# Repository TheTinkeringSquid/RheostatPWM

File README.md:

# Dodge B2500 Instrument Cluster LED PWM Dimmer

Small RP2040-based PWM dimmer board for a 1996 Dodge B2500 instrument cluster
LED conversion. It reads the factory headlight rheostat as an analog input and
drives the cluster illumination feed with a protected high-side 12 V PWM output.

> **Cluster illumination only.** This board is not for exterior lighting, brake
> lights, turn signals, airbags, engine controls, or any safety-critical
> circuit.

---

## How it works

```
factory full 12 V illumination/headlamp-switched feed  -> J1 VIN_RAW
factory dimmer/rheostat analog output                  -> J1 DIM_IN  (sense only)
board high-side 12 V PWM output                        -> J1 PWM_OUT -> cluster LED +
cluster/chassis ground                                 -> J1 GND
```

The factory rheostat no longer powers the cluster lamps. It is read as a
low-current analog control signal through a high-impedance divider into the
XIAO RP2040 ADC. Firmware maps that voltage through a gamma curve to a high-side
PWM output (P-channel MOSFET Q1 driven by N-MOSFET Q2), so the lamp grounds stay
factory.

### Connector (J1)

| Pin | Net        | Description                                            |
|----:|------------|--------------------------------------------------------|
| 1   | `VIN_RAW`  | Fused full 12 V illumination/headlight-switched feed   |
| 2   | `GND`      | Chassis/cluster ground                                 |
| 3   | `DIM_IN`   | Factory rheostat output, sense only                    |
| 4   | `PWM_OUT`  | PWM +12 V output to cluster LED illumination feed      |
| 5   | `IGN_SENSE`| Optional lights-on signal (future firmware; DNP parts) |

### Install concept

1. Identify the factory cluster illumination/dimmer feed with a multimeter and
   wiring diagram.
2. Cut or depin the cluster illumination feed so the rheostat no longer powers
   the LED bulbs directly.
3. Connect the **vehicle/rheostat side** of that wire to `DIM_IN`.
4. Connect the **cluster/lamp side** of that wire to `PWM_OUT`.
5. Power the board from a fused full-bright illumination feed that is hot when
   park/headlights are on — **not** from the dimmed rheostat output.
6. Ground the board to the cluster/chassis ground.

> Do **not** power the microcontroller from `DIM_IN`; it may brown out when the
> rheostat is turned down.
>
> If the factory dimmer turns out to be low-side, already-PWM, or multiplexed
> rather than a simple variable positive voltage, **stop** and revise the input
> circuit instead of forcing this design.

---

## Repository layout

```
.
├── README.md
├── firmware/                     PlatformIO project (Seeed XIAO RP2040)
│   ├── platformio.ini
│   └── src/main.cpp
└── hardware/
    ├── kicad/
    │   ├── b2500_cluster_pwm_dimmer.kicad_pro / .kicad_sch / .kicad_pcb
    │   ├── b2500_cluster_pwm_dimmer_schematic.pdf
    │   ├── pcb_top.png
    │   └── symbols_and_footprints/b2500.pretty/   (XIAO + Pololu module footprints)
    ├── scripts/                  generators (re-create the design deterministically)
    │   ├── netlist.py            single source of truth for the netlist
    │   ├── gen_sch.py            -> kicad_sch
    │   ├── gen_pcb.py            -> kicad_pcb
    │   ├── gen_bom.py            -> BOM CSV
    │   └── export_fab.py         -> gerbers + drill + BOM (run after routing)
    ├── gerbers/                  fabrication output (generated after routing)
    ├── fabrication_notes.md
    └── b2500_cluster_pwm_dimmer_bom.csv
```

The KiCad schematic, board, and BOM are generated by the scripts in
`hardware/scripts/`. They share `netlist.py` so the schematic and board can
never drift apart. Regenerate with:

```powershell
python hardware/scripts/gen_sch.py                       # schematic
& "C:/Program Files/KiCad/10.0/bin/python.exe" hardware/scripts/gen_pcb.py   # board (needs KiCad's Python)
python hardware/scripts/gen_bom.py                       # BOM CSV
```

---

## Firmware

Built with PlatformIO for the Seeed Studio XIAO RP2040 (Arduino / Earle
Philhower RP2040 core).

```bash
cd firmware
pio run            # build
pio run -t upload  # flash (board in UF2 bootloader, or via USB)
pio device monitor # 115200 baud serial debug
```

Key calibration constants live at the top of `firmware/src/main.cpp`
(`ADC_OFF_THRESHOLD`, `ADC_MIN_INPUT`, `ADC_MAX_INPUT`, `DUTY_MIN`, `GAMMA`,
`PWM_FREQ_HZ`, plus `REVERSE_DIMMER_DIRECTION`). Tune them on the bench against
the real dimmer using the serial output. PWM defaults to 976 Hz (in the
500 Hz–2 kHz target band).

---

## PCB

The board is **fully routed and DRC-clean** (0 violations, 0 unconnected) —
2 layers, 94 × 62 mm, ground pour on both. `hardware/scripts/gen_pcb.py`
places every part, pours ground, and routes all nets with a built-in
collision-aware router (Manhattan + maze fallback): high-current nets
(`VIN_RAW`, `PWM_OUT`, `VIN_PROT`) at 1.5 mm, signals at 0.4 mm. The gerbers and
drill files in `hardware/gerbers/` are ready to send to a fabricator.

You don't need to touch KiCad to get the board made. If you *want* to inspect or
tweak it:

1. Open `hardware/kicad/b2500_cluster_pwm_dimmer.kicad_pro` in KiCad 10.
2. Make changes, run DRC, then regenerate fabrication output:

   ```powershell
   python hardware/scripts/export_fab.py
   ```

   This runs DRC, writes gerbers + Excellon drill to `hardware/gerbers/`, and
   regenerates the BOM. (Re-running `gen_pcb.py` regenerates the whole board
   from scratch and will discard manual KiCad edits.)

### Ordering the board

Zip the contents of `hardware/gerbers/` and upload to any PCB fab (JLCPCB,
PCBWay, OSH Park, Aisler, etc.): 2-layer, 1.6 mm, 1 oz copper (2 oz is a nice
upgrade for the power path), HASL or ENIG. See
[hardware/fabrication_notes.md](hardware/fabrication_notes.md) for the full
spec, assembly notes, and the bench/in-vehicle test procedures.

---

## Deviations from the original brief

- **Board size** is ~94 × 62 mm, not the 50 × 35 mm target. The through-hole
  part set (5-pos 5.08 mm terminal block, TO-220, two modules, radial cap, seven
  test points, button) does not fit smaller while staying hand-solderable. A
  compact SMD-MOSFET / smaller-connector variant is a sensible future revision.
- **Q1 gate pull-up R6 is 10 k (brief said 47 k)** and a **DNP R10/C5 RC snubber
  footprint** sits across `PWM_OUT` — both for a cleaner, better-defined
  high-side switching edge with less ringing/EMI. Fit the snubber only if the
  bench scope shows ringing.
- **The buck regulator (U2) mounts off-board**, wired to a labeled 3-pin
  header (`VIN`/`GND`/`VOUT`). A footprint audit against the Pololu module
  showed its on-board land is easy to get wrong (6 pins incl. an offset PG, two
  GNDs); a wired connection is order-proof and far safer to assemble by hand.
- **Two M3 mounting holes** (per the BOM, M1–M2), placed diagonally — the
  terminal block fills the left edge, so a top-left hole was not possible.
- The board is routed by a **purpose-built script router**, not by hand in
  KiCad. It is DRC-clean and electrically complete, but the trace paths are
  Manhattan/maze-style rather than artistically dressed; feel free to prettify
  in the GUI if you re-spin.
- The XIAO USB-C port is not on a board edge; for in-place reflashing, prefer
  the UF2 bootloader or relocate U1 to an edge in a future revision.

## Safety

- Always fuse `VIN_RAW` (inline blade fuse in the harness — F1 is not on the
  board). Size it to the measured LED cluster current.
- Do not route the cluster output back through the factory rheostat.
- Do not connect USB while the board is vehicle-powered unless JP1 is open / the
  D3 isolation diode is fitted, to avoid 5 V backfeed.
- This is not OEM-grade load-dump protection. The TVS + wide-input regulator
  reduce risk but do not eliminate it.
- Carry a bypass jumper during early testing so the cluster lamps can be
  restored if the board fails.

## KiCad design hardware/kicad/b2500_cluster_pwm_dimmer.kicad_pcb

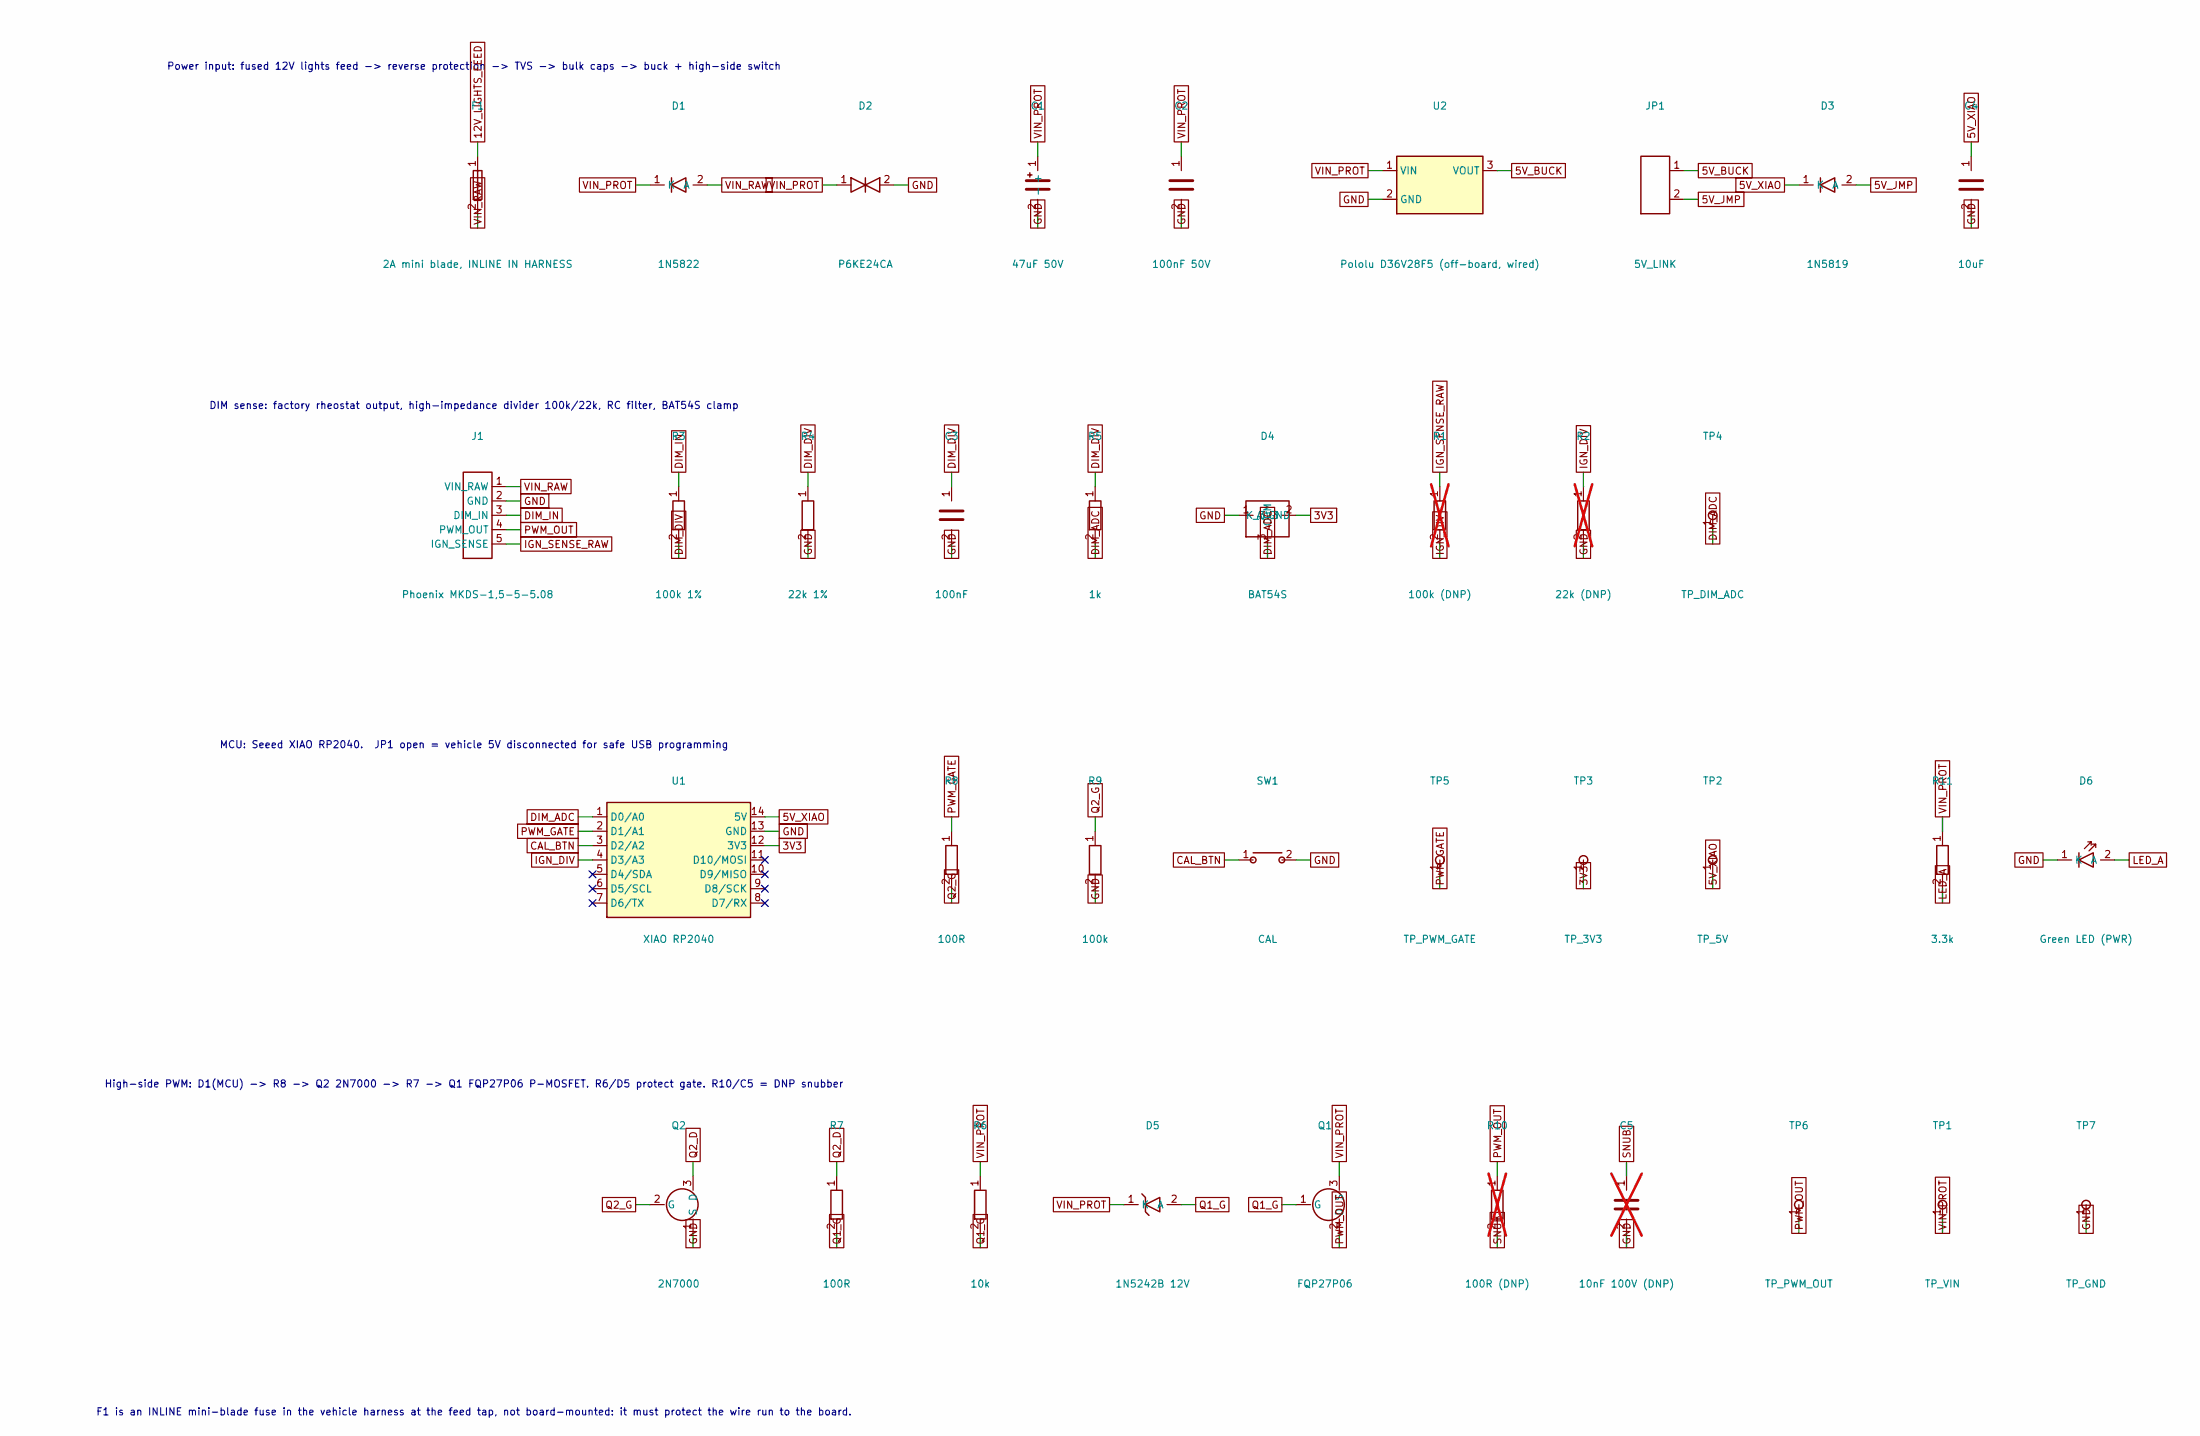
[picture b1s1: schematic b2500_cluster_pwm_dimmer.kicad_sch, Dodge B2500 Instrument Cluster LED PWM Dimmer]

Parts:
C1: 47uF 50V; CP_Radial_D6.3mm_P2.50mm
C2: 100nF 50V; C_0805_2012Metric_Pad1.18x1.45mm_HandSolder
C3: 100nF; C_0805_2012Metric_Pad1.18x1.45mm_HandSolder
C4: 10uF; C_0805_2012Metric_Pad1.18x1.45mm_HandSolder
C5: 10nF 100V (DNP); C_0805_2012Metric_Pad1.18x1.45mm_HandSolder; not fitted
D1: 1N5822; D_DO-201AD_P15.24mm_Horizontal
D2: P6KE24CA; D_DO-15_P10.16mm_Horizontal
D3: 1N5819; D_DO-41_SOD81_P10.16mm_Horizontal
D4: BAT54S; SOT-23
D5: 1N5242B 12V; D_DO-35_SOD27_P7.62mm_Horizontal
D6: Green LED (PWR); LED_D3.0mm
F1: 2A mini blade, INLINE IN HARNESS
J1: Phoenix MKDS-1,5-5-5.08; TerminalBlock_Phoenix_MKDS-1,5-5-5.08_1x05_P5.08mm_Horizont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
JP1: 5V_LINK; PinHeader_1x02_P2.54mm_Vertical
Q1: FQP27P06; TO-220-3_Vertical
Q2: 2N7000; TO-92_Inline_Wide
R1: 100k (DNP); R_0805_2012Metric_Pad1.20x1.40mm_HandSolder; not fitted
R2: 22k (DNP); R_0805_2012Metric_Pad1.20x1.40mm_HandSolder; not fitted
R3: 100k 1%; R_0805_2012Metric_Pad1.20x1.40mm_HandSolder
R4: 22k 1%; R_0805_2012Metric_Pad1.20x1.40mm_HandSolder
R5: 1k; R_0805_2012Metric_Pad1.20x1.40mm_HandSolder
R6: 10k; R_0805_2012Metric_Pad1.20x1.40mm_HandSolder
R7, R8: 100R; R_0805_2012Metric_Pad1.20x1.40mm_HandSolder
R9: 100k; R_0805_2012Metric_Pad1.20x1.40mm_HandSolder
R10: 100R (DNP); R_0805_2012Metric_Pad1.20x1.40mm_HandSolder; not fitted
R11: 3.3k; R_0805_2012Metric_Pad1.20x1.40mm_HandSolder
SW1: CAL; SW_PUSH_6mm
TP1: TP_VIN; TestPoint_THTPad_D1.5mm_Drill0.7mm
TP2: TP_5V; TestPoint_THTPad_D1.5mm_Drill0.7mm
TP3: TP_3V3; TestPoint_THTPad_D1.5mm_Drill0.7mm
TP4: TP_DIM_ADC; TestPoint_THTPad_D1.5mm_Drill0.7mm
TP5: TP_PWM_GATE; TestPoint_THTPad_D1.5mm_Drill0.7mm
TP6: TP_PWM_OUT; TestPoint_THTPad_D1.5mm_Drill0.7mm
TP7: TP_GND; TestPoint_THTPad_D1.5mm_Drill0.7mm
U1: XIAO RP2040; XIAO_RP2040_THT
U2: Pololu D36V28F5 (off-board, wired); PinHeader_1x03_P2.54mm_Vertical

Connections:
3V3: D4.2 (K_3V3), TP3.1, U1.12 (3V3)
5V_BUCK: JP1.1, U2.3 (VOUT)
5V_JMP: D3.2 (A), JP1.2
5V_XIAO: C4.1, D3.1 (K), TP2.1, U1.14 (5V)
CAL_BTN: SW1.1, U1.3 (D2/A2)
DIM_ADC: D4.3 (COM), R5.2, TP4.1, U1.1 (D0/A0)
DIM_DIV: C3.1, R3.2, R4.1, R5.1
DIM_IN: J1.3 (DIM_IN), R3.1
GND: C1.2 (-), C2.2, C3.2, C4.2, C5.2, D2.2, D4.1 (A_GND), D6.1 (K), J1.2 (GND), Q2.1 (S), R2.2, R4.2, R9.2, SW1.2, TP7.1, U1.13 (GND), U2.2 (GND)
IGN_DIV: R1.2, R2.1, U1.4 (D3/A3)
IGN_SENSE_RAW: J1.5 (IGN_SENSE), R1.1
LED_A: D6.2 (A), R11.2
PWM_GATE: R8.1, TP5.1, U1.2 (D1/A1)
PWM_OUT: J1.4 (PWM_OUT), Q1.2 (D), R10.1, TP6.1
Q1_G: D5.2 (A), Q1.1 (G), R6.2, R7.2
Q2_D: Q2.3 (D), R7.1
Q2_G: Q2.2 (G), R8.2, R9.1
SNUB: C5.1, R10.2
VIN_PROT: C1.1 (+), C2.1, D1.1 (K), D2.1, D5.1 (K), Q1.3 (S), R6.1, R11.1, TP1.1, U2.1 (VIN)
VIN_RAW: D1.2 (A), F1.2, J1.1 (VIN_RAW)

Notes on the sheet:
Power input: fused 12V lights feed -> reverse protection -> TVS -> bulk caps -> buck + high-side switch
DIM sense: factory rheostat output, high-impedance divider 100k/22k, RC filter, BAT54S clamp
MCU: Seeed XIAO RP2040. JP1 open = vehicle 5V disconnected for safe USB programming
High-side PWM: D1(MCU) -> R8 -> Q2 2N7000 -> R7 -> Q1 FQP27P06 P-MOSFET. R6/D5 protect gate. R10/C5 = DNP snubber
F1 is an INLINE mini-blade fuse in the vehicle harness at the feed tap, not board-mounted: it must protect the wire run to the board.

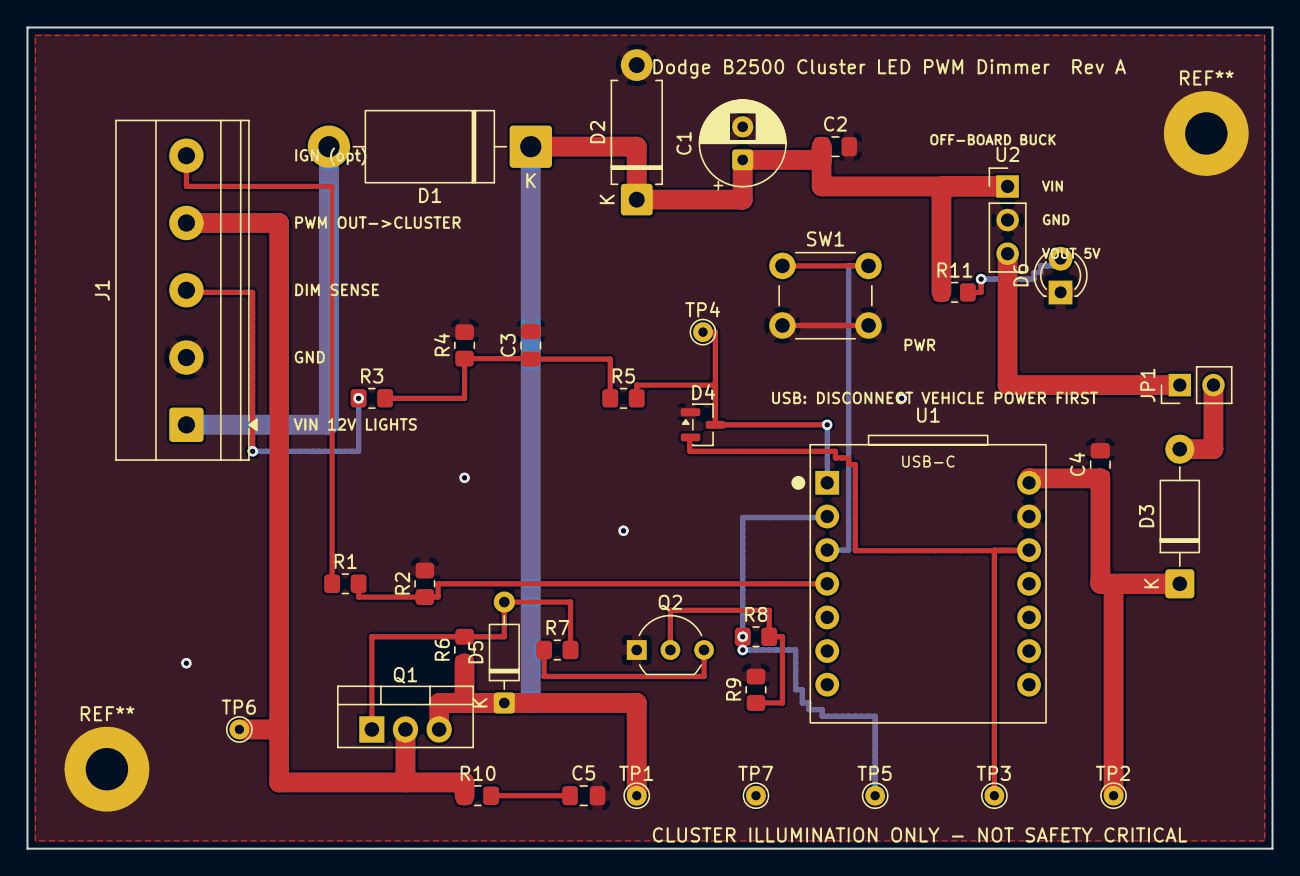
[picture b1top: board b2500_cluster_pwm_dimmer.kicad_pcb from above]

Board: 2 copper layers, 94.0 x 62.0 mm, 36 parts (0 on the bottom side), 20 nets.

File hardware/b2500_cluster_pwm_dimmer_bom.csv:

Refs,Qty,Value,Footprint,Fit,Notes
C1,1,47uF 50V,Capacitor_THT:CP_Radial_D6.3mm_P2.50mm,FIT,
C2,1,100nF 50V,Capacitor_SMD:C_0805_2012Metric_Pad1.18x1.45mm_HandSolder,FIT,
C3,1,100nF,Capacitor_SMD:C_0805_2012Metric_Pad1.18x1.45mm_HandSolder,FIT,
C4,1,10uF,Capacitor_SMD:C_0805_2012Metric_Pad1.18x1.45mm_HandSolder,FIT,
C5,1,10nF 100V (DNP),Capacitor_SMD:C_0805_2012Metric_Pad1.18x1.45mm_HandSolder,DNP,DNP RC snubber across PWM_OUT (fit only if edge ringing)
D1,1,1N5822,Diode_THT:D_DO-201AD_P15.24mm_Horizontal,FIT,"reverse-polarity series Schottky, >=3A >=40V"
D2,1,P6KE24CA,Diode_THT:D_DO-15_P10.16mm_Horizontal,FIT,TVS across protected VIN-GND
D3,1,1N5819,Diode_THT:D_DO-41_SOD81_P10.16mm_Horizontal,FIT,optional 5V isolation diode (USB backfeed)
D4,1,BAT54S,Package_TO_SOT_SMD:SOT-23,FIT,ADC clamp to 3V3/GND
D5,1,1N5242B 12V,Diode_THT:D_DO-35_SOD27_P7.62mm_Horizontal,FIT,"12V zener, Q1 gate-source protection"
D6,1,Green LED (PWR),LED_THT:LED_D3.0mm,FIT,green power-on LED (lit whenever 12V is present); 3mm through-hole
F1,1,"2A mini blade, INLINE IN HARNESS",,OFF-BOARD,OFF-BOARD: inline blade fuse in the vehicle harness; size to LED current
J1,1,"Phoenix MKDS-1,5-5-5.08","TerminalBlock_Phoenix:TerminalBlock_Phoenix_MKDS-1,5-5-5.08_1x05_P5.08mm_Horizontal",FIT,5-pos 5.08mm pluggable terminal (or locking automotive conn)
JP1,1,5V_LINK,Connector_PinHeader_2.54mm:PinHeader_1x02_P2.54mm_Vertical,FIT,open to isolate vehicle 5V during USB programming
Q1,1,FQP27P06,Package_TO_SOT_THT:TO-220-3_Vertical,FIT,">=40V Vds, >=2A, low Rds(on); TO-220"
Q2,1,2N7000,Package_TO_SOT_THT:TO-92_Inline_Wide,FIT,small logic-level N-MOSFET / 2N7000
R1,1,100k (DNP),Resistor_SMD:R_0805_2012Metric_Pad1.20x1.40mm_HandSolder,DNP,DNP IGN-sense divider (future firmware)
R10,1,100R (DNP),Resistor_SMD:R_0805_2012Metric_Pad1.20x1.40mm_HandSolder,DNP,DNP RC snubber across PWM_OUT (fit only if edge ringing)
R11,1,3.3k,Resistor_SMD:R_0805_2012Metric_Pad1.20x1.40mm_HandSolder,FIT,series resistor for D6 power LED (~3 mA at 12 V)
R2,1,22k (DNP),Resistor_SMD:R_0805_2012Metric_Pad1.20x1.40mm_HandSolder,DNP,DNP IGN-sense divider (future firmware)
R3,1,100k 1%,Resistor_SMD:R_0805_2012Metric_Pad1.20x1.40mm_HandSolder,FIT,
R4,1,22k 1%,Resistor_SMD:R_0805_2012Metric_Pad1.20x1.40mm_HandSolder,FIT,
R5,1,1k,Resistor_SMD:R_0805_2012Metric_Pad1.20x1.40mm_HandSolder,FIT,
R6,1,10k,Resistor_SMD:R_0805_2012Metric_Pad1.20x1.40mm_HandSolder,FIT,
"R7,R8",2,100R,Resistor_SMD:R_0805_2012Metric_Pad1.20x1.40mm_HandSolder,FIT,
R9,1,100k,Resistor_SMD:R_0805_2012Metric_Pad1.20x1.40mm_HandSolder,FIT,
SW1,1,CAL,Button_Switch_THT:SW_PUSH_6mm,FIT,
TP1,1,TP_VIN,TestPoint:TestPoint_THTPad_D1.5mm_Drill0.7mm,FIT,
TP2,1,TP_5V,TestPoint:TestPoint_THTPad_D1.5mm_Drill0.7mm,FIT,
TP3,1,TP_3V3,TestPoint:TestPoint_THTPad_D1.5mm_Drill0.7mm,FIT,
TP4,1,TP_DIM_ADC,TestPoint:TestPoint_THTPad_D1.5mm_Drill0.7mm,FIT,
TP5,1,TP_PWM_GATE,TestPoint:TestPoint_THTPad_D1.5mm_Drill0.7mm,FIT,
TP6,1,TP_PWM_OUT,TestPoint:TestPoint_THTPad_D1.5mm_Drill0.7mm,FIT,
TP7,1,TP_GND,TestPoint:TestPoint_THTPad_D1.5mm_Drill0.7mm,FIT,
U1,1,XIAO RP2040,b2500:XIAO_RP2040_THT,FIT,Seeed XIAO RP2040 module on 2x7 socket headers
U2,1,"Pololu D36V28F5 (off-board, wired)",Connector_PinHeader_2.54mm:PinHeader_1x03_P2.54mm_Vertical,FIT,"Pololu D36V28F5 buck module, mounted OFF-BOARD; wire its VIN/GND/VOUT to the 3-pin header (match label to label)"
